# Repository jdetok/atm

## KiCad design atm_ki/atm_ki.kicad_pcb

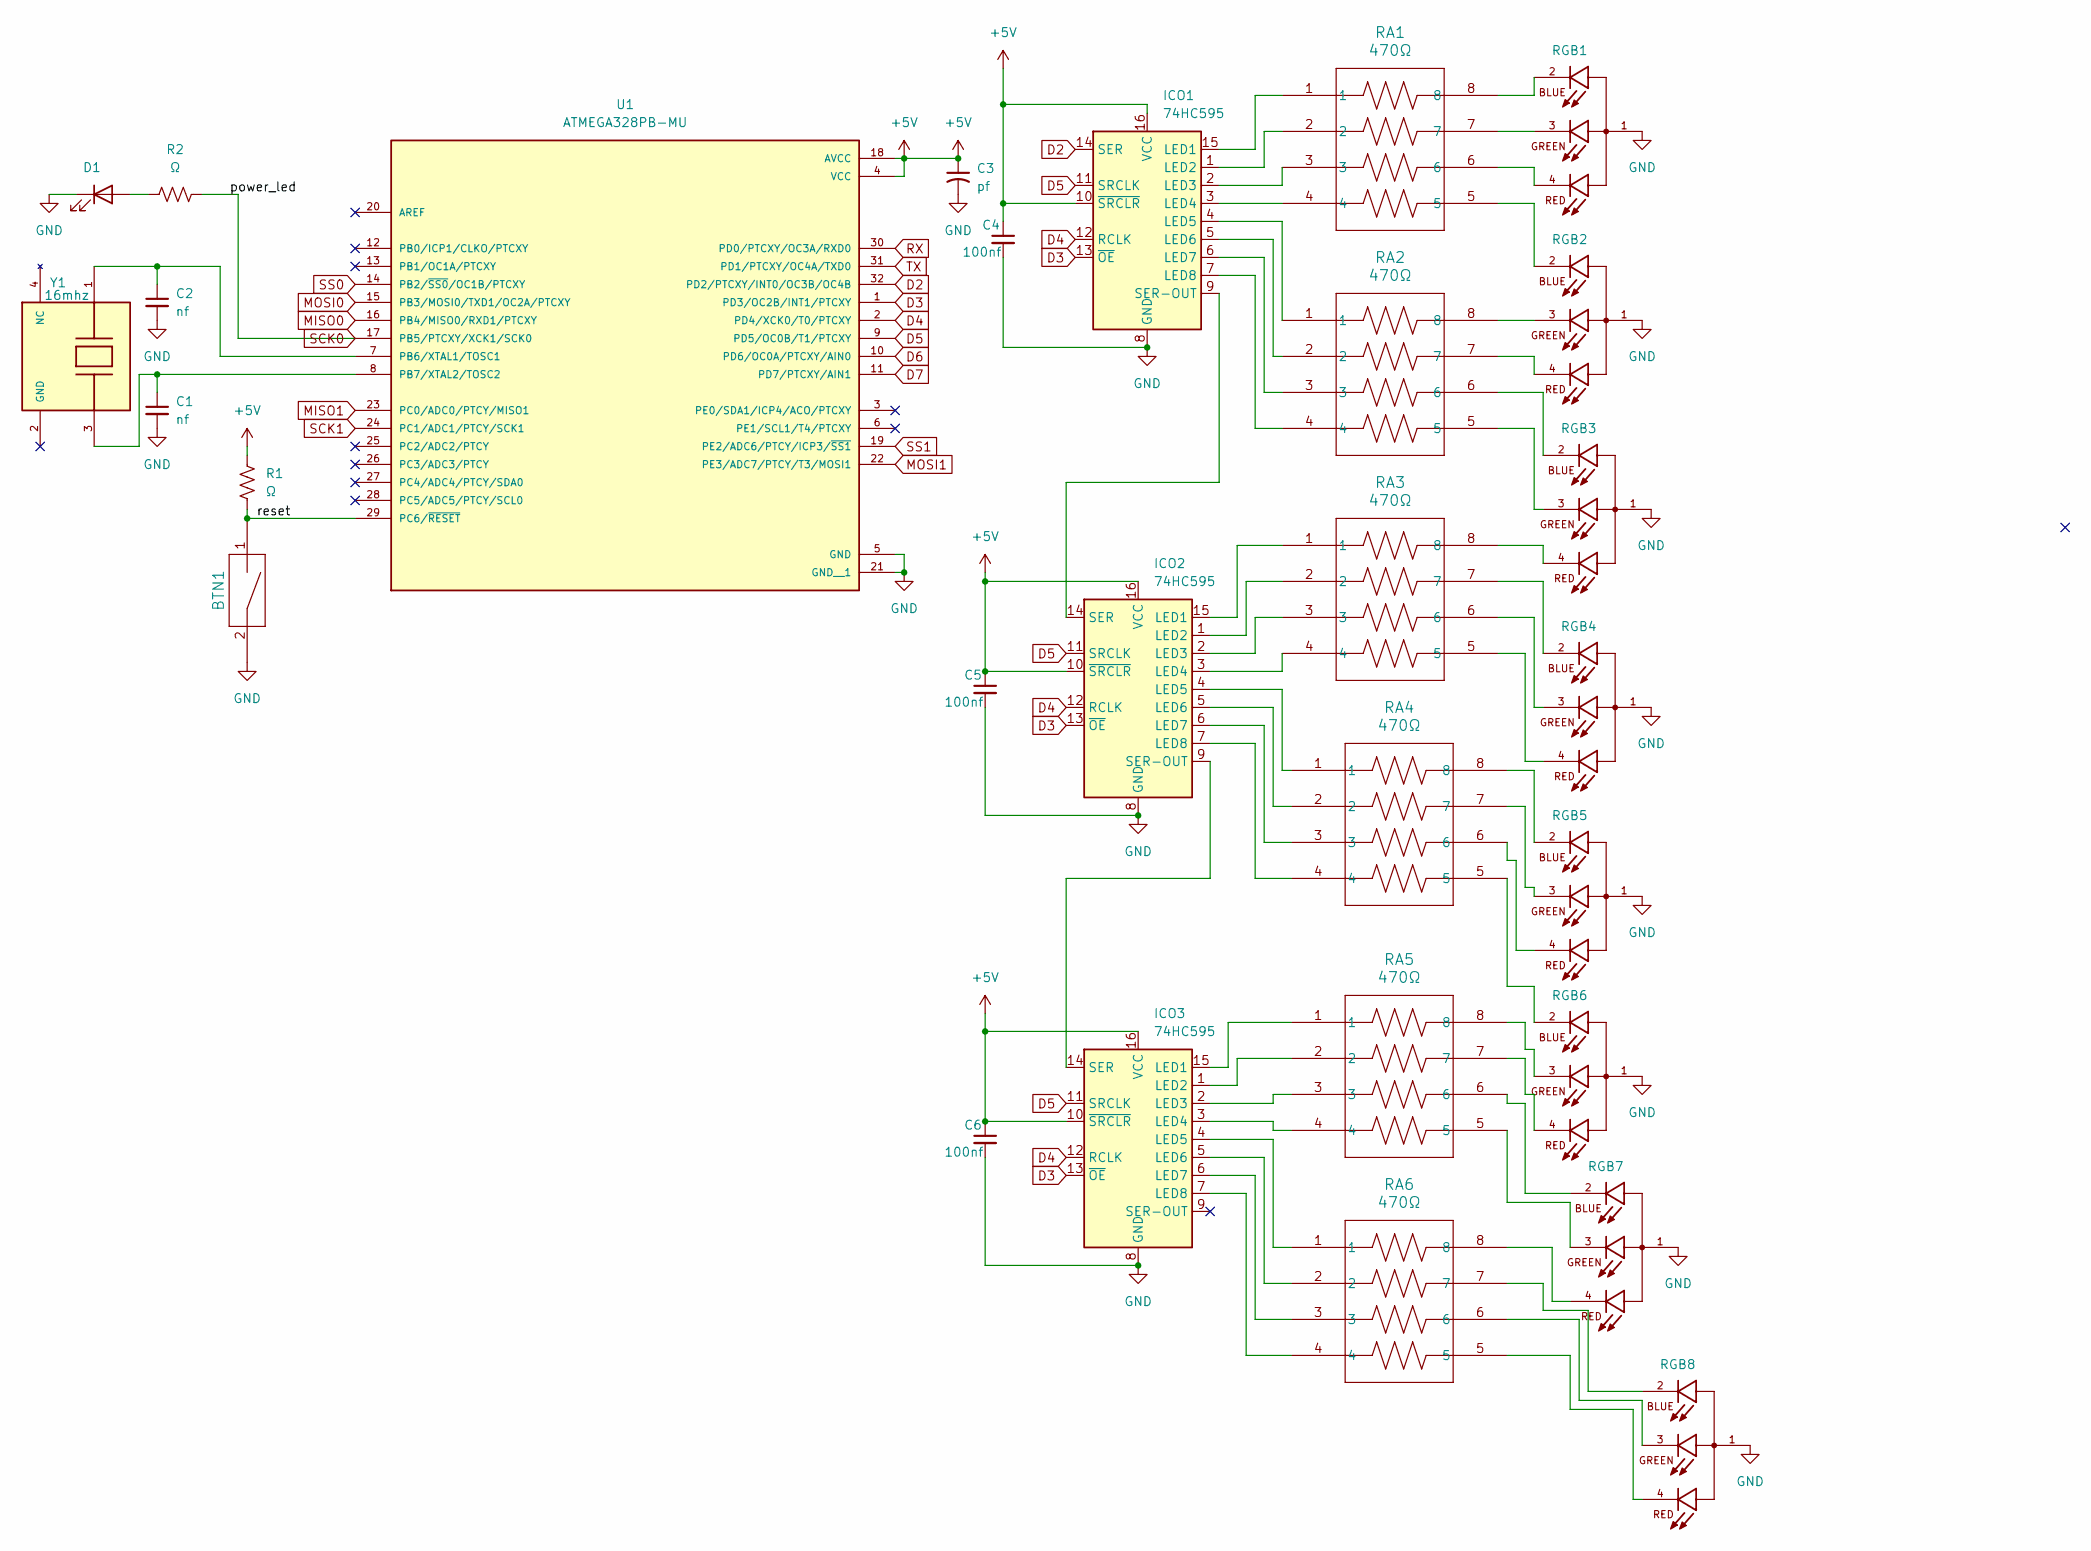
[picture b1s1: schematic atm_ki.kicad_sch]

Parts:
BTN1: BTN_R-667995; BTN_R-667995_MIT
C1, C2: nf; CAPC1608X90
C3: pf; WCAP-ASLI_5X5.5_DXL_
C4, C5, C6: 100nf; CAPC1608X90
D1: led_small; LED_LTST-C170GKT_LTO
ICO1, ICO2, ICO3: 74HC595; sop16_hc595
R1, R2: Ω; RESC1607X60N
RA1, RA2, RA3, RA4, RA5, RA6: 470Ω; C_ARRAY_EXB28V_PAN
RGB1, RGB2, RGB3, RGB4, RGB5, RGB6, RGB7, RGB8: rgb; LED_CLMVC-FKA-CL1D1L71BB7C3C3; PARTREV 14
U1: ATMEGA328PB-MU; QFN50P500X500X90-33N; PARTREV C
Y1: 16mhz; OSC_CX2016DB16000D0WZRC1; PARTREV October 2024

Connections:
+5V: C3.1, C4.1, C5.1, C6.1, ICO1.10 (~SRCLR), ICO1.16 (VCC), ICO2.10 (~SRCLR), ICO2.16 (VCC), ICO3.10 (~SRCLR), ICO3.16 (VCC), R1.1, U1.4 (VCC), U1.18 (AVCC)
/reset: BTN1.1, R1.2, U1.29 (PC6/~RESET)
D2: ICO1.14 (SER), U1.32 (PD2/PTCXY/INT0/OC3B/OC4B)
D3: ICO1.13 (~OE), ICO2.13 (~OE), ICO3.13 (~OE), U1.1 (PD3/OC2B/INT1/PTCXY)
D4: ICO1.12 (RCLK), ICO2.12 (RCLK), ICO3.12 (RCLK), U1.2 (PD4/XCK0/T0/PTCXY)
D5: ICO1.11 (SRCLK), ICO2.11 (SRCLK), ICO3.11 (SRCLK), U1.9 (PD5/OC0B/T1/PTCXY)
D6: U1.10 (PD6/OC0A/PTCXY/AIN0)
D7: U1.11 (PD7/PTCXY/AIN1)
GND: BTN1.2, C1.2, C2.2, C3.2, C4.2, C5.2, C6.2, D1.1 (K), ICO1.8 (GND), ICO2.8 (GND), ICO3.8 (GND), RGB1.1, RGB2.1, RGB3.1, RGB4.1, RGB5.1, RGB6.1, RGB7.1, RGB8.1, U1.5 (GND), U1.21 (GND__1)
MISO0: U1.16 (PB4/MISO0/RXD1/PTCXY)
MISO1: U1.23 (PC0/ADC0/PTCY/MISO1)
MOSI0: U1.15 (PB3/MOSI0/TXD1/OC2A/PTCXY)
MOSI1: U1.22 (PE3/ADC7/PTCY/T3/MOSI1)
unnamed: D1.2 (A), R2.1
unnamed: ICO1.15 (LED1), RA1.1
unnamed: ICO1.1 (LED2), RA1.2
unnamed: ICO1.2 (LED3), RA1.3
unnamed: ICO1.3 (LED4), RA1.4
unnamed: ICO1.4 (LED5), RA2.1
unnamed: ICO1.5 (LED6), RA2.2
unnamed: ICO1.6 (LED7), RA2.3
unnamed: ICO1.7 (LED8), RA2.4
unnamed: ICO1.9 (SER-OUT), ICO2.14 (SER)
unnamed: ICO2.15 (LED1), RA3.1
unnamed: ICO2.1 (LED2), RA3.2
unnamed: ICO2.2 (LED3), RA3.3
unnamed: ICO2.3 (LED4), RA3.4
unnamed: ICO2.4 (LED5), RA4.1
unnamed: ICO2.5 (LED6), RA4.2
unnamed: ICO2.6 (LED7), RA4.3
unnamed: ICO2.7 (LED8), RA4.4
unnamed: ICO2.9 (SER-OUT), ICO3.14 (SER)
unnamed: ICO3.15 (LED1), RA5.1
unnamed: ICO3.1 (LED2), RA5.2
unnamed: ICO3.2 (LED3), RA5.3
unnamed: ICO3.3 (LED4), RA5.4
unnamed: ICO3.4 (LED5), RA6.1
unnamed: ICO3.5 (LED6), RA6.2
unnamed: ICO3.6 (LED7), RA6.3
unnamed: ICO3.7 (LED8), RA6.4
unnamed: RA1.5, RGB2.2
unnamed: RA1.6, RGB1.4
unnamed: RA1.7, RGB1.3
unnamed: RA1.8, RGB1.2
unnamed: RA2.5, RGB3.3
unnamed: RA2.6, RGB3.2
unnamed: RA2.7, RGB2.4
unnamed: RA2.8, RGB2.3
unnamed: RA3.5, RGB4.4
unnamed: RA3.6, RGB4.3
unnamed: RA3.7, RGB4.2
unnamed: RA3.8, RGB3.4
unnamed: RA4.5, RGB6.2
unnamed: RA4.6, RGB5.4
unnamed: RA4.7, RGB5.3
unnamed: RA4.8, RGB5.2
unnamed: RA5.5, RGB7.3
unnamed: RA5.6, RGB7.2
unnamed: RA5.7, RGB6.4
unnamed: RA5.8, RGB6.3
unnamed: RA6.5, RGB8.4
unnamed: RA6.6, RGB8.3
unnamed: RA6.7, RGB8.2
unnamed: RA6.8, RGB7.4
unnamed: C2.1, U1.7 (PB6/XTAL1/TOSC1), Y1.1
unnamed: C1.1, U1.8 (PB7/XTAL2/TOSC2), Y1.3
RX: U1.30 (PD0/PTCXY/OC3A/RXD0)
SCK0: R2.2, U1.17 (PB5/PTCXY/XCK1/SCK0)
SCK1: U1.24 (PC1/ADC1/PTCY/SCK1)
SS0: U1.14 (PB2/~SS0/OC1B/PTCXY)
SS1: U1.19 (PE2/ADC6/PTCY/ICP3/~SS1)
TX: U1.31 (PD1/PTCXY/OC4A/TXD0)

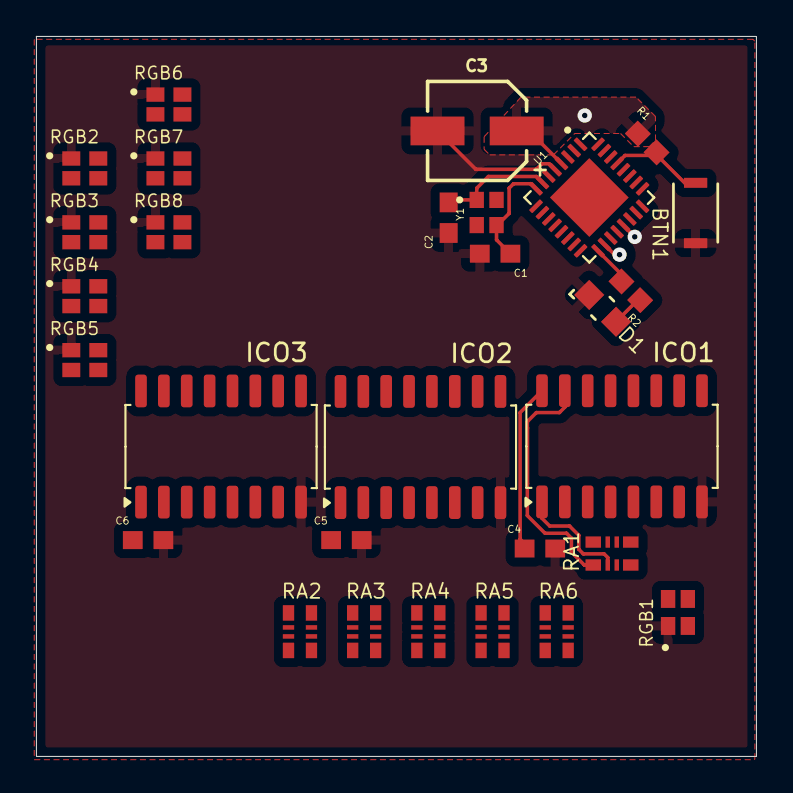
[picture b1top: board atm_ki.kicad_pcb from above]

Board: 2 copper layers, 40.0 x 40.0 mm, 29 parts (0 on the bottom side), 61 nets.

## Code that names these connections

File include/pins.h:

#pragma once

#define D2 (1 << PD2)
#define D3 (1 << PD3)
#define D4 (1 << PD4)
#define D5 (1 << PD5)

#define D13 (1 << PB5)

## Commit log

2026-02-01 blink without lib
2026-02-01 setup and onoff funcs, still only blink
